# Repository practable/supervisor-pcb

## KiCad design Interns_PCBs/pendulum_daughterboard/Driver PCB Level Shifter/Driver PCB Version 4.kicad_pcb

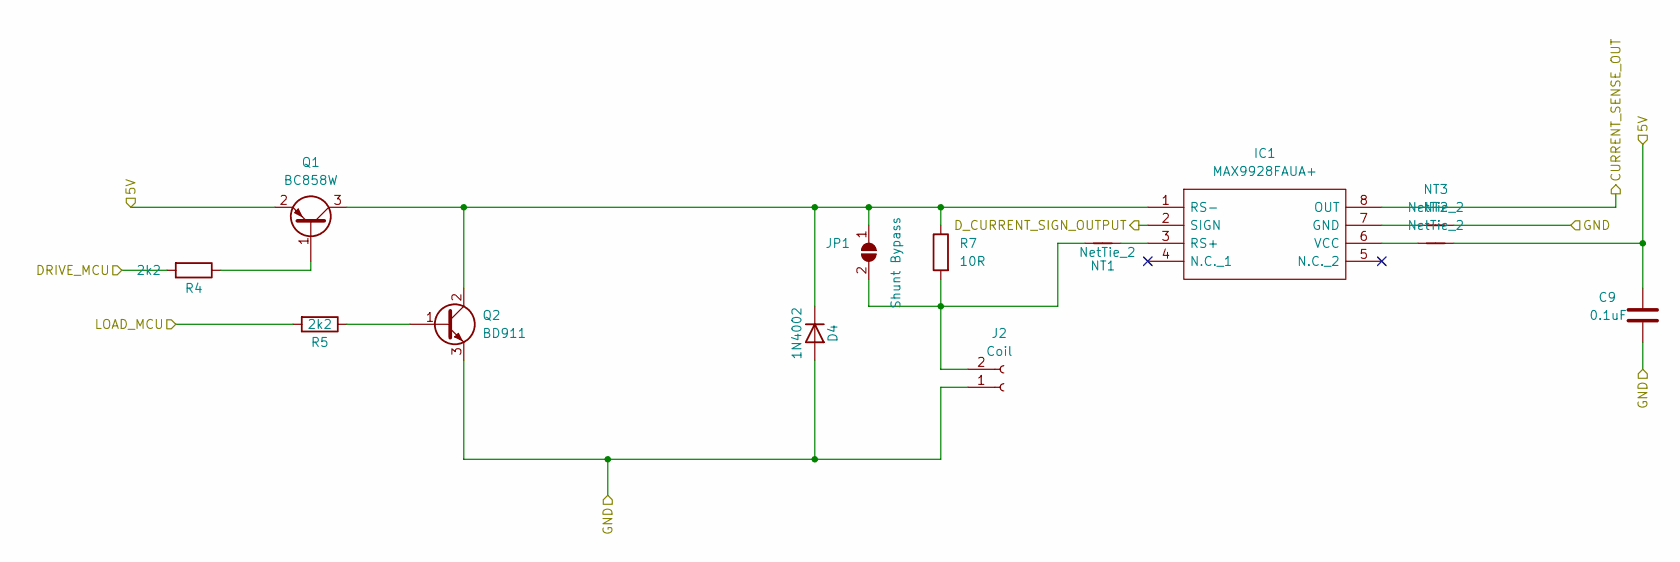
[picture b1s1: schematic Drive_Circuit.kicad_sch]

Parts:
C9: 0.1uF; C_0805_2012Metric_Pad1.18x1.45mm_HandSolder
D4: 1N4002; D_T-1_P5.08mm_Horizontal
IC1: MAX9928FAUA+; SOP65P490X110-8N; Manufacturer_Part_Number MAX9928FAUA+; Mouser Part Number 700-MAX9928FAUA
J2: Coil; RSPROPenduinoTerminal
JP1: Shunt Bypass; SolderJumper-2_P1.3mm_Open_Pad1.0x1.5mm
NT1, NT2, NT3: NetTie_2; NetTie-2_SMD_Pad0.5mm
Q1: BC858W; SOT-23
Q2: BD911; SOT-23
R4, R5: 2k2; R_0805_2012Metric_Pad1.20x1.40mm_HandSolder
R7: 10R; R_0805_2012Metric_Pad1.20x1.40mm_HandSolder

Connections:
DRIVE_GND: C9.2, D4.1 (A), J2.1, NT3.2, Q2.3 (E); also elsewhere on the board
DRIVE_OUT: R4.2; also elsewhere on the board
LOAD_OUT: R5.2; also elsewhere on the board
unnamed 13: D4.2 (K), IC1.1 (RS-), JP1.1 (A), Q1.3 (C), Q2.2 (C), R7.1; also elsewhere on the board
unnamed: IC1.7 (GND), NT3.1
unnamed 16: IC1.3 (RS+), NT1.2; also elsewhere on the board
unnamed 17: IC1.6 (VCC), NT2.1; also elsewhere on the board
unnamed: J2.2, JP1.2 (B), NT1.1, R7.2
unnamed: Q1.1 (B), R4.1
unnamed: Q2.1 (B), R5.1

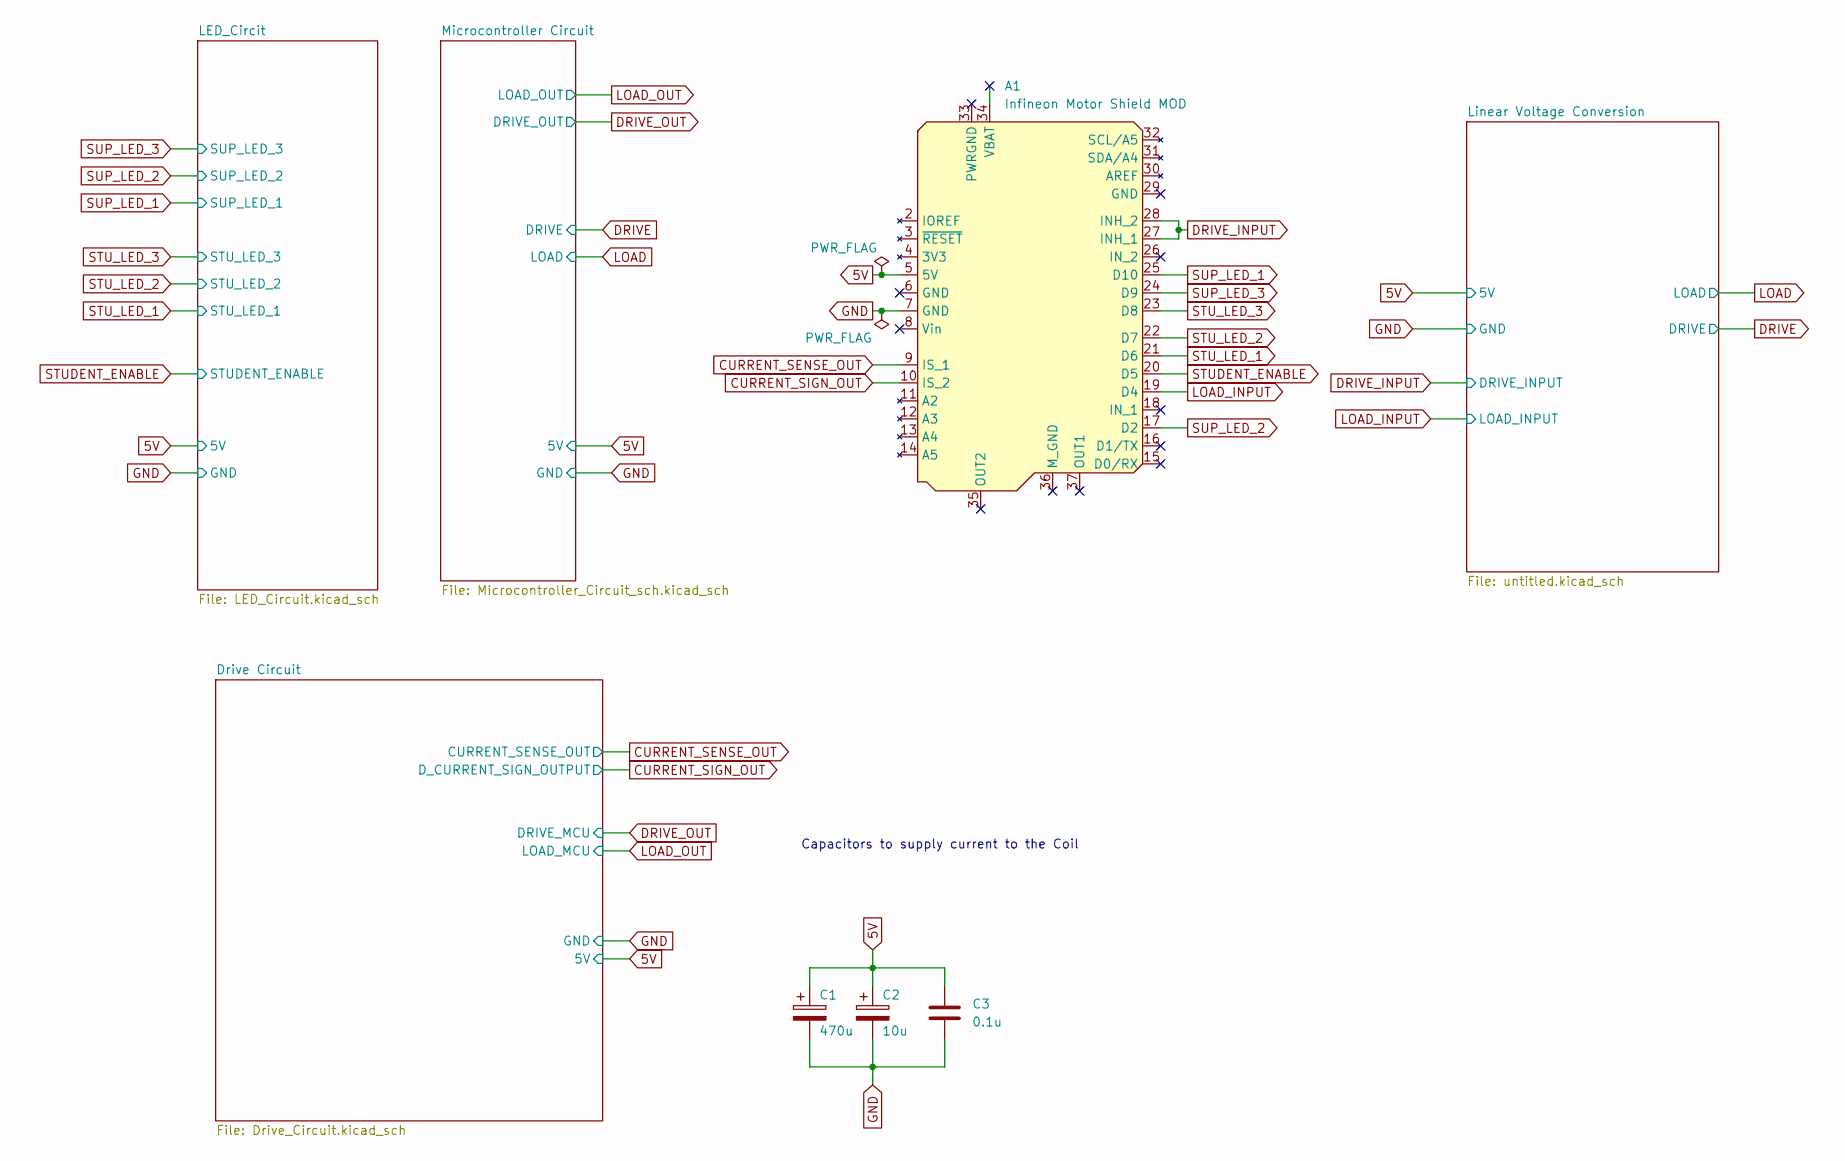
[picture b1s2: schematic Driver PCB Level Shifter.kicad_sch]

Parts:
A1: Infineon Motor Shield MOD; Infineon Motor Sheild hiddenPins
C1: 470u; C_Elec_8x10.2
C2: 10u; CP_Elec_3x5.3
C3: 0.1u; C_0805_2012Metric_Pad1.18x1.45mm_HandSolder

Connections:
CURRENT_SENSE_OUT: A1.9 (IS_1); also elsewhere on the board
CURRENT_SIGN_OUT: A1.10 (IS_2); also elsewhere on the board
DRIVE_GND: A1.7 (GND), C1.2, C2.2, C3.2; also elsewhere on the board
DRIVE_INPUT: A1.27 (INH_1), A1.28 (INH_2); also elsewhere on the board
LOAD_INPUT: A1.19 (D4); also elsewhere on the board
STUDENT_ENABLE: A1.20 (D5); also elsewhere on the board
STU_LED_1: A1.21 (D6); also elsewhere on the board
STU_LED_2: A1.22 (D7); also elsewhere on the board
STU_LED_3: A1.23 (D8); also elsewhere on the board
SUP_LED_1: A1.25 (D10); also elsewhere on the board
SUP_LED_2: A1.17 (D2); also elsewhere on the board
SUP_LED_3: A1.24 (D9); also elsewhere on the board

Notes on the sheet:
Capacitors to supply current to the Coil

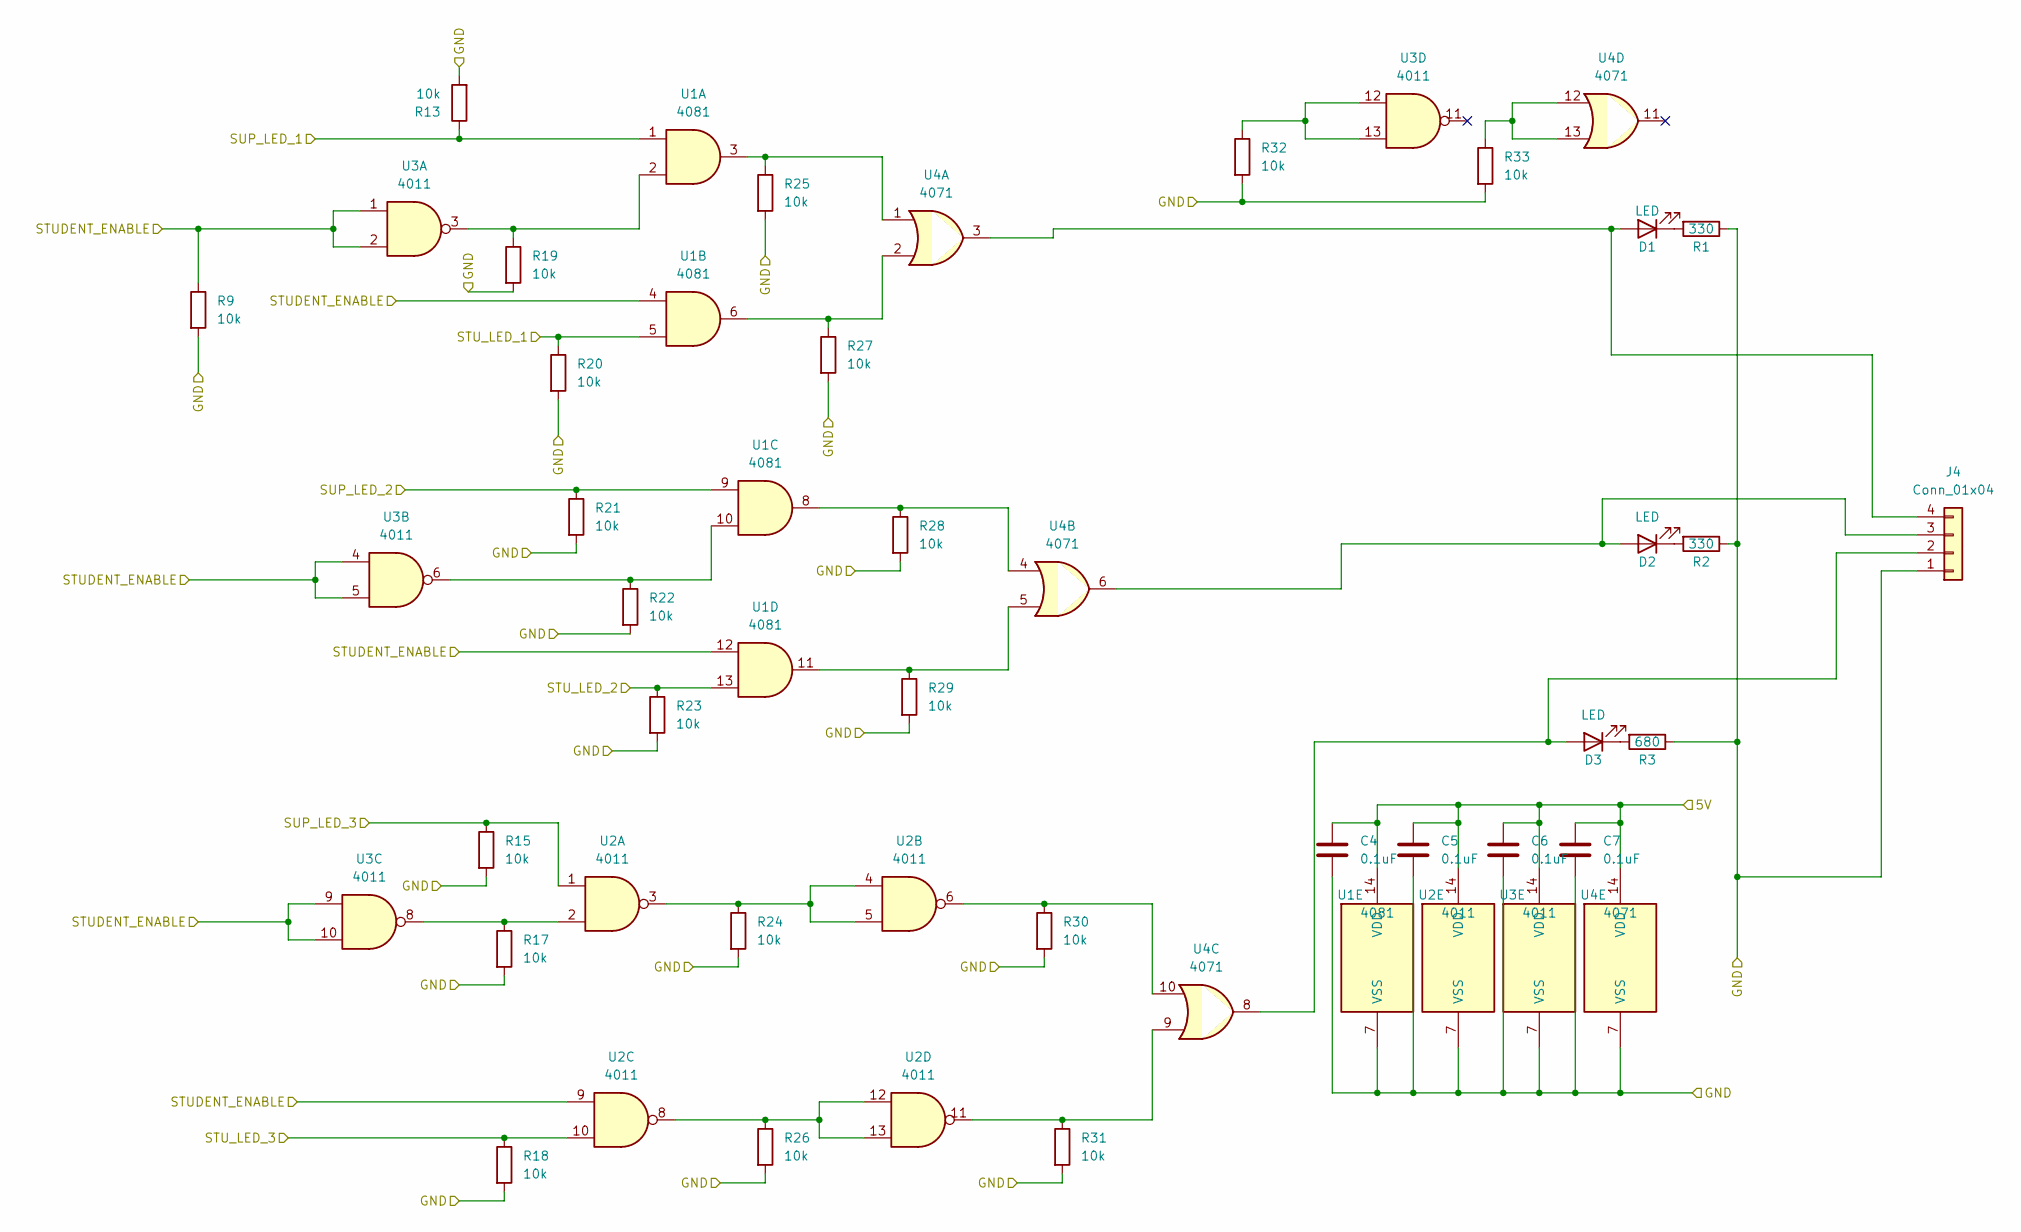
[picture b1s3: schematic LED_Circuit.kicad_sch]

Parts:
C4, C5, C6, C7: 0.1uF; C_0805_2012Metric_Pad1.18x1.45mm_HandSolder
D1, D2, D3: LED; LED_0805_2012Metric_Pad1.15x1.40mm_HandSolder
J4: Conn_01x04; PinHeader_1x04_P2.54mm_Vertical
R1, R2: 330; R_0805_2012Metric_Pad1.20x1.40mm_HandSolder
R3: 680; R_0805_2012Metric_Pad1.20x1.40mm_HandSolder
R9, R13, R15, R17, R18, R19, R20, R21, R22, R23, R24, R25, R26, R27, R28, R29, R30, R31, R32, R33: 10k; R_0805_2012Metric_Pad1.20x1.40mm_HandSolder
U1: 4081; SOIC127P600X175-14N
U2, U3: 4011; SOIC127P600X175-14N
U4: 4071; SOIC127P600X175-14N

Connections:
DRIVE_GND: C4.2, C5.2, C6.2, C7.2, J4.1, R1.1, R2.1, R3.1, R9.2, R13.2, R15.2, R17.2, R18.2, R19.2, R20.2, R21.2, R22.2, R23.2, R24.2, R25.2, R26.2, R27.2, R28.2, R29.2, R30.2, R31.2, R32.2, R33.2, U1.7 (VSS), U2.7 (VSS), U3.7 (VSS), U4.7 (VSS); also elsewhere on the board
unnamed: D1.1 (K), R1.2
unnamed: D1.2 (A), J4.4, U4.3
unnamed: D2.1 (K), R2.2
unnamed: D2.2 (A), J4.3, U4.6
unnamed: D3.1 (K), R3.2
unnamed: D3.2 (A), J4.2, U4.8
unnamed: R17.1, U2.2, U3.8
unnamed: R19.1, U1.2, U3.3
unnamed: R22.1, U1.10, U3.6
unnamed: R24.1, U2.3, U2.4, U2.5
unnamed: R25.1, U1.3, U4.1
unnamed: R26.1, U2.8, U2.12, U2.13
unnamed: R27.1, U1.6, U4.2
unnamed: R28.1, U1.8, U4.4
unnamed: R29.1, U1.11, U4.5
unnamed: R30.1, U2.6, U4.10
unnamed: R31.1, U2.11, U4.9
unnamed: R32.1, U3.12, U3.13
unnamed: R33.1, U4.12, U4.13
STUDENT_ENABLE: R9.1, U1.4, U1.12, U2.9, U3.1, U3.2, U3.4, U3.5, U3.9, U3.10; also elsewhere on the board
STU_LED_1: R20.1, U1.5; also elsewhere on the board
STU_LED_2: R23.1, U1.13; also elsewhere on the board
STU_LED_3: R18.1, U2.10; also elsewhere on the board
SUP_LED_1: R13.1, U1.1; also elsewhere on the board
SUP_LED_2: R21.1, U1.9; also elsewhere on the board
SUP_LED_3: R15.1, U2.1; also elsewhere on the board

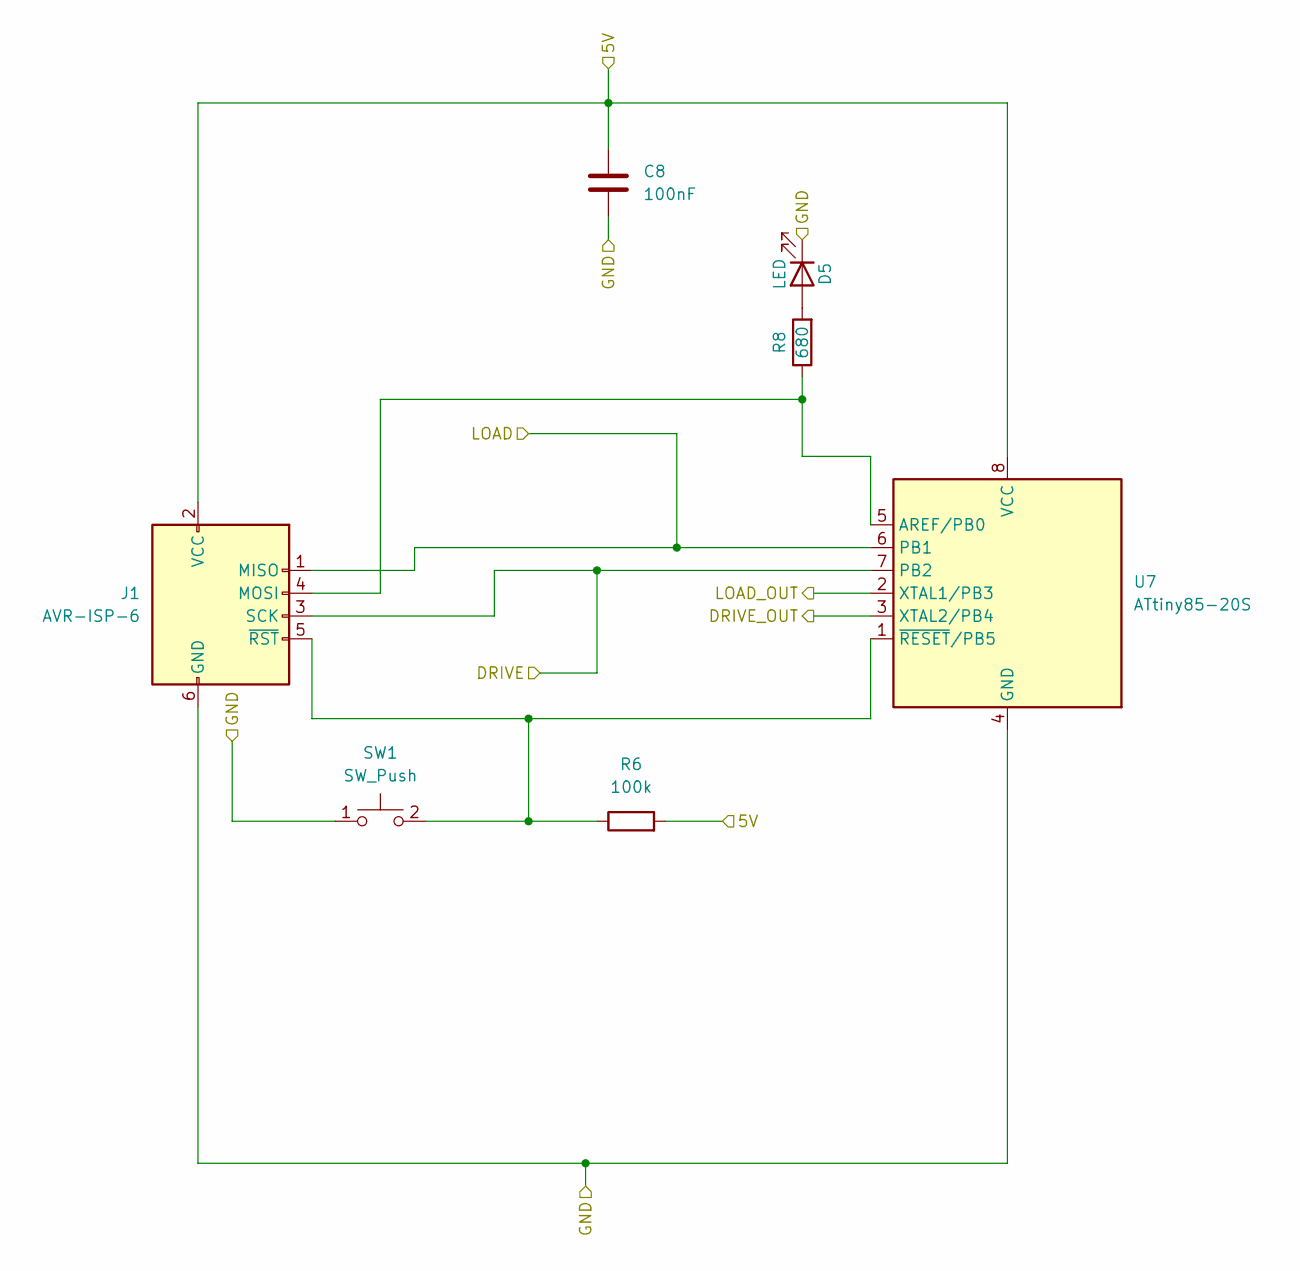
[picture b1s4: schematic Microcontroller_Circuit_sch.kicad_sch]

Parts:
C8: 100nF; C_0805_2012Metric_Pad1.18x1.45mm_HandSolder
D5: LED; LED_0805_2012Metric_Pad1.15x1.40mm_HandSolder
J1: AVR-ISP-6; PinHeader_2x03_P2.54mm_Vertical
R6: 100k; R_0805_2012Metric_Pad1.20x1.40mm_HandSolder
R8: 680; R_0805_2012Metric_Pad1.20x1.40mm_HandSolder
SW1: SW_Push; 13019319
U7: ATtiny85-20S; SOIC-8W_5.3x5.3mm_P1.27mm

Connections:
DRIVE_GND: C8.2, D5.1 (K), J1.6 (GND), SW1.1, U7.4 (GND); also elsewhere on the board
DRIVE_INPUT: J1.3 (SCK), U7.7 (PB2); also elsewhere on the board
LOAD_INPUT: J1.1 (MISO), U7.6 (PB1); also elsewhere on the board
unnamed: D5.2 (A), R8.2
unnamed 18: J1.4 (MOSI), R8.1, U7.5 (AREF/PB0); also elsewhere on the board
unnamed 19: J1.5 (~RST), R6.1, SW1.2, U7.1 (~RESET/PB5); also elsewhere on the board

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
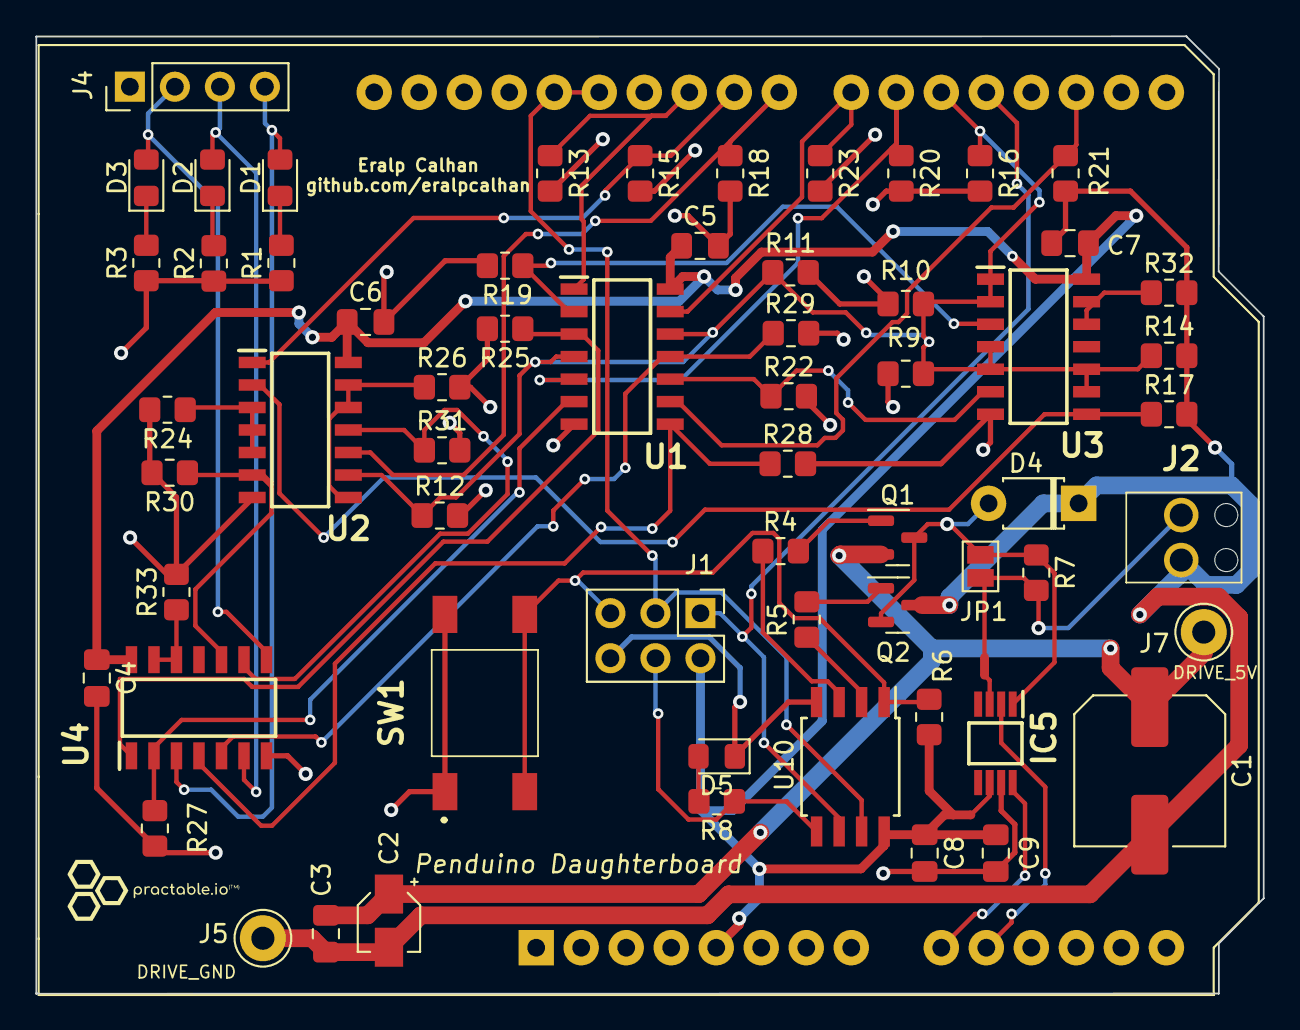
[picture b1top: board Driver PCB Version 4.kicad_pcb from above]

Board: 2 copper layers, 69.2 x 54.0 mm, 65 parts (0 on the bottom side), 44 nets.

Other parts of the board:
IC5: MAX9928FAUA+; SOP65P490X110-8N
J5: DRIVE_GND; Pin_D1.3mm_L11.0mm
J7: DRIVE_5V_IN; Pin_D1.3mm_L11.0mm
R10, R11, R12, R14, R16: 10k; R_0805_2012Metric_Pad1.20x1.40mm_HandSolder
U10: ATtiny85-20S; SOIC-8W_5.3x5.3mm_P1.27mm

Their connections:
CURRENT_SENSE_OUT: IC5.8 (OUT); also elsewhere on the board
CURRENT_SIGN_OUT: IC5.2 (SIGN); also elsewhere on the board
DRIVE_GND: IC5.7 (GND), J5.1, R10.2, R11.2, R12.2, R14.2, R16.2, U10.4 (GND); also elsewhere on the board
DRIVE_INPUT: U10.7 (PB2); also elsewhere on the board
DRIVE_OUT: U10.3 (XTAL2/PB4); also elsewhere on the board
LOAD_INPUT: U10.6 (PB1); also elsewhere on the board
LOAD_OUT: U10.2 (XTAL1/PB3); also elsewhere on the board
unnamed 13: IC5.1 (RS-); also elsewhere on the board
unnamed 16: IC5.3 (RS+); also elsewhere on the board
unnamed 17: IC5.6 (VCC); also elsewhere on the board
unnamed 18: U10.5 (AREF/PB0); also elsewhere on the board
unnamed 19: U10.1 (~RESET/PB5); also elsewhere on the board
STUDENT_ENABLE: R10.1, R11.1, R12.1, R14.1, R16.1; also elsewhere on the board

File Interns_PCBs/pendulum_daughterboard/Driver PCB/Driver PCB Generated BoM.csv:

"Source:","C:\Users\mcalhan\Documents\GitHub\RemoteLabs_Supervisor_PCB\pendulum_daughterboard\Driver PCB\Driver PCB.kicad_sch"
"Date:","23/06/2022 15:05:01"
"Tool:","Eeschema (6.0.5)"
"Generator:","C:\Program Files\KiCad\6.0\bin\scripting\plugins/bom_csv_grouped_by_value_with_fp.py"
"Component Count:","36"
"Ref","Qnty","Value","Cmp name","Footprint","Description","Vendor"
"A1, ","1","Infineon Motor Shield MOD","Infineon Motor Shield MOD","Audio_Module:Infineon Motor Sheild hiddenPins","Infineon Motor Driver Shield for Arduino Uno",""
"C1, ","1","460u","C_Polarized","Capacitor_SMD:C_0805_2012Metric_Pad1.18x1.45mm_HandSolder","Polarized capacitor",""
"C2, ","1","10u","C_Polarized","Capacitor_SMD:C_0805_2012Metric_Pad1.18x1.45mm_HandSolder","Polarized capacitor",""
"C3, ","1","0.1u","C","Capacitor_SMD:C_0805_2012Metric_Pad1.18x1.45mm_HandSolder","Unpolarized capacitor",""
"C4, C5, C6, C7, C8, ","5","100nF","C","Capacitor_SMD:C_0805_2012Metric_Pad1.18x1.45mm_HandSolder","Unpolarized capacitor",""
"C9, ","1","0.1uF","C","Capacitor_SMD:C_0805_2012Metric_Pad1.18x1.45mm_HandSolder","Unpolarized capacitor",""
"D1, D2, D3, ","3","LED","LED","LED_SMD:LED_0805_2012Metric_Pad1.15x1.40mm_HandSolder","Light emitting diode",""
"D4, ","1","1N4002","DIODE","Diode_SMD:D_0603_1608Metric_Pad1.05x0.95mm_HandSolder","Diode, anode on pin 1, for simulation only!",""
"IC1, ","1","AND GATES","CD74HC08QM96EP","ICPINS:SOIC127P600X175-14N","Enhanced Product Quadruple 2-Input Positive-And Gates",""
"IC2, ","1","NAND (Used as AND)","MC74ACT00DG","ICPINS:SOIC127P600X175-14N","ON SEMICONDUCTOR - MC74ACT00DG - IC, QUAD NAND GATE, 2I/P, SOIC-14",""
"IC3, ","1","NAND (Used as Inverter)","MC74ACT00DG","ICPINS:SOIC127P600X175-14N","ON SEMICONDUCTOR - MC74ACT00DG - IC, QUAD NAND GATE, 2I/P, SOIC-14",""
"IC4, ","1","OR ","MC74ACT00DG","ICPINS:SOIC127P600X175-14N","ON SEMICONDUCTOR - MC74ACT00DG - IC, QUAD NAND GATE, 2I/P, SOIC-14",""
"IC5, ","1","MAX9928FAUA+","MAX9928FAUA+","Sensor_Current:SOP65P490X110-8N","Maxim MAX9928FAUA+, Current Sensing Amplifier Single Bidirectional, Unidirectional 8-Pin uMAX",""
"J1, ","1","AVR-ISP-6","AVR-ISP-6","Connector_PinHeader_2.00mm:PinHeader_2x03_P2.00mm_Vertical","Atmel 6-pin ISP connector",""
"J2, ","1","Coil","Conn_01x02_Female","TerminalBlock_TE-Connectivity:TerminalBlock_TE_282834-2_1x02_P2.54mm_Horizontal","Generic connector, single row, 01x02, script generated (kicad-library-utils/schlib/autogen/connector/)",""
"J4, ","1","Conn_01x04","Conn_01x04","TerminalBlock_TE-Connectivity:TerminalBlock_TE_282834-4_1x04_P2.54mm_Horizontal","Generic connector, single row, 01x04, script generated (kicad-library-utils/schlib/autogen/connector/)",""
"J5, ","1","DRIVE_GND","Conn_01x01","Connector_Pin:Pin_D1.3mm_L11.0mm","Generic connector, single row, 01x01, script generated (kicad-library-utils/schlib/autogen/connector/)",""
"J7, ","1","DRIVE_5V_IN","Conn_01x01","Connector_Pin:Pin_D1.3mm_L11.0mm","Generic connector, single row, 01x01, script generated (kicad-library-utils/schlib/autogen/connector/)",""
"JP1, ","1","Shunt Bypass","SolderJumper_2_Open","Jumper:SolderJumper-2_P1.3mm_Open_Pad1.0x1.5mm","Solder Jumper, 2-pole, open",""
"Q1, ","1","BC557","BC557","Package_TO_SOT_SMD:SOT-523","0.1A Ic, 45V Vce, PNP Small Signal Transistor, TO-92",""
"Q2, ","1","BC547","BC547","Package_TO_SOT_SMD:SOT-523","0.1A Ic, 45V Vce, Small Signal NPN Transistor, TO-92",""
"R1, R2, R3, ","3","120","R","Resistor_SMD:R_0805_2012Metric_Pad1.20x1.40mm_HandSolder","Resistor",""
"R4, R5, ","2","2k2","R","Resistor_SMD:R_0805_2012Metric_Pad1.20x1.40mm_HandSolder","Resistor",""
"R6, ","1","100k","R","Resistor_SMD:R_0805_2012Metric_Pad1.20x1.40mm_HandSolder","Resistor",""
"R7, ","1","10R","R","Resistor_SMD:R_0805_2012Metric_Pad1.20x1.40mm_HandSolder","Resistor",""
"SW1, ","1","SW_Push","SW_Push","Button_Switch_SMD:13019319","Push button switch, generic, two pins",""
"U10, ","1","ATtiny85-20S","ATtiny85-20S","Package_SO:SOIC-8W_5.3x5.3mm_P1.27mm","20MHz, 8kB Flash, 512B SRAM, 512B EEPROM, debugWIRE, SOIC-8W",""

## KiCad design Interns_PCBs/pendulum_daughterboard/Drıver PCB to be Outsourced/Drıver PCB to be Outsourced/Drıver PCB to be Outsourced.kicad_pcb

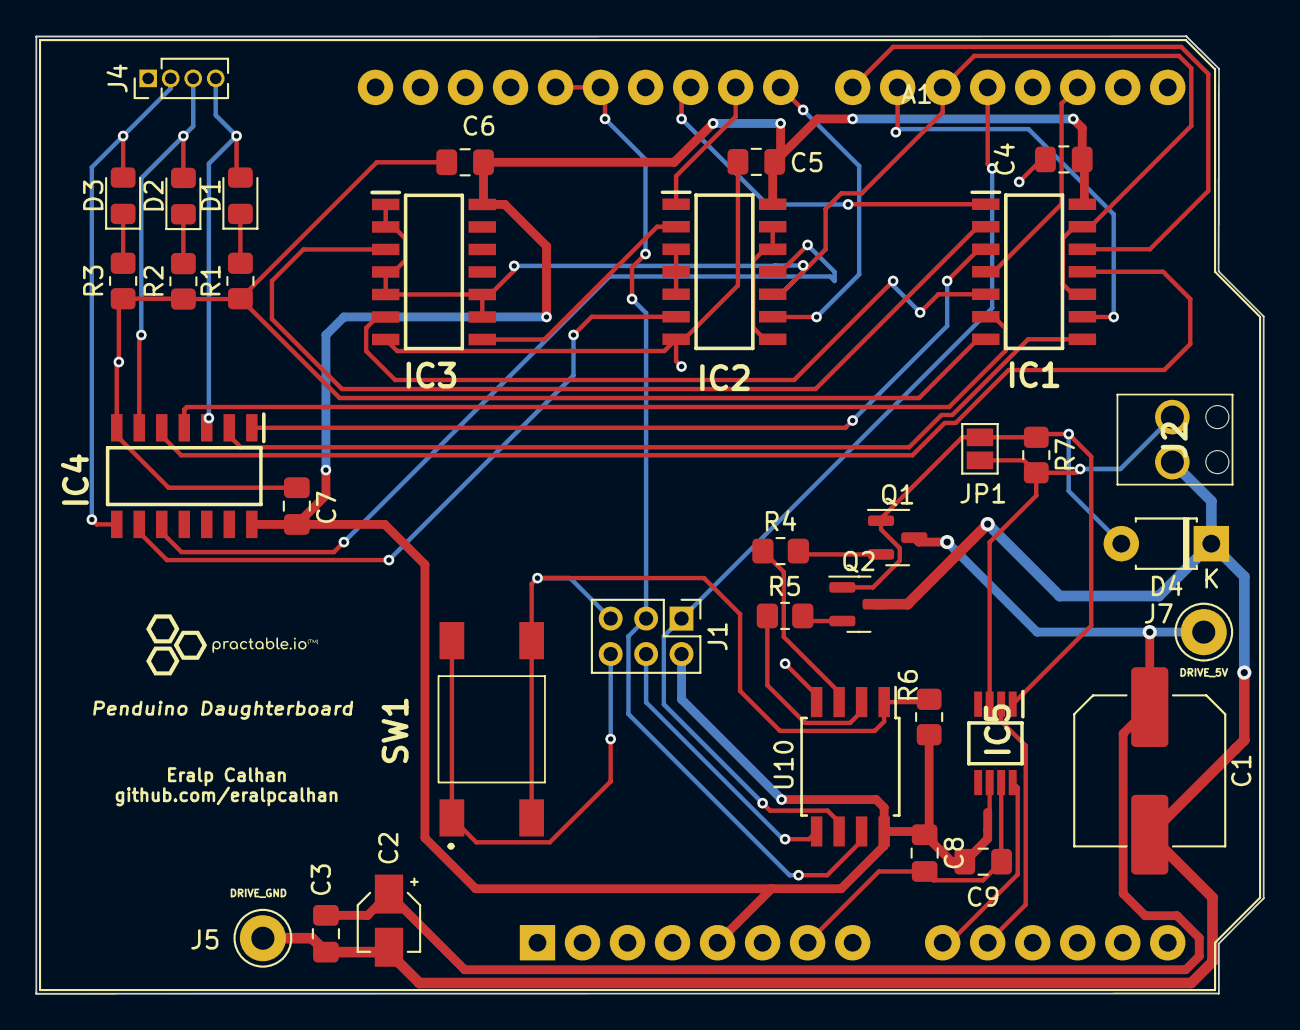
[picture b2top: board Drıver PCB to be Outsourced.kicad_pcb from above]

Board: 2 copper layers, 69.2 x 54.0 mm, 37 parts (0 on the bottom side), 41 nets.

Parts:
A1: Infineon Motor Shield MOD; Infineon Motor Sheild hiddenPins
C1: 470u; C_Elec_8x10.2
C2: 10u; CP_Elec_3x5.3
C3: 0.1u; C_0805_2012Metric_Pad1.18x1.45mm_HandSolder
C4, C5, C6, C7, C8: 100nF; C_0805_2012Metric_Pad1.18x1.45mm_HandSolder
C9: 0.1uF; C_0805_2012Metric_Pad1.18x1.45mm_HandSolder
D1, D2, D3: LED; LED_0805_2012Metric_Pad1.15x1.40mm_HandSolder
D4: 1N4002; D_T-1_P5.08mm_Horizontal
IC1: AND GATES; SOIC127P600X175-14N
IC2: NAND (Used as AND); SOIC127P600X175-14N
IC3: NAND (Used as Inverter); SOIC127P600X175-14N
IC4: OR; SOIC127P600X175-14N
IC5: MAX9928FAUA+; SOP65P490X110-8N
J1: AVR-ISP-6; PinHeader_2x03_P2.00mm_Vertical
J2: Coil; RSPROPenduinoTerminal
J4: Conn_01x04; PinHeader_1x04_P1.27mm_Vertical
J5: DRIVE_GND; Pin_D1.3mm_L11.0mm
J7: DRIVE_5V_IN; Pin_D1.3mm_L11.0mm
JP1: Shunt Bypass; SolderJumper-2_P1.3mm_Open_Pad1.0x1.5mm
NT1: NetTie_2; NetTie-2_SMD_Pad0.5mm
Q1: BC557; SOT-23
Q2: BC547; SOT-23
R1, R2, R3: 120; R_0805_2012Metric_Pad1.20x1.40mm_HandSolder
R4, R5: 2k2; R_0805_2012Metric_Pad1.20x1.40mm_HandSolder
R6: 100k; R_0805_2012Metric_Pad1.20x1.40mm_HandSolder
R7: 10R; R_0805_2012Metric_Pad1.20x1.40mm_HandSolder
SW1: SW_Push; 13019319
U10: ATtiny85-20S; SOIC-8W_5.3x5.3mm_P1.27mm

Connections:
AND_STU_LED_1: IC1.8 (3Y), IC4.2 (B1)
AND_STU_LED_2: IC1.11 (4Y), IC4.5 (B2)
AND_STU_LED_3: IC2.11 (Y4), IC4.10 (B3)
AND_SUP_LED_1: IC1.3 (1Y), IC4.1 (A1)
AND_SUP_LED_2: IC1.6 (2Y), IC4.4 (A2)
AND_SUP_LED_3: IC2.6 (Y2), IC4.9 (A3)
CURRENT_SENSE_OUT: A1.9 (IS_1), IC5.8 (OUT)
CURRENT_SIGN_OUT: A1.10 (IS_2), IC5.2 (SIGN)
DRIVE_5V: C1.1, C2.1, C3.1, J7.1, Q1.3 (E)
DRIVE_GND: C1.2, C2.2, C3.2, D4.1 (A), J2.1, J5.1, Q2.3 (E)
DRIVE_INPUT: A1.27 (INH_1), A1.28 (INH_2), J1.3 (SCK), U10.7 (PB2)
DRIVE_MCU: R4.2, U10.3 (XTAL2/PB4)
D_5V: A1.5 (5V), C4.1, C5.1, C6.1, C7.1, C8.1, C9.1, IC1.14 (VCC), IC2.14 (VCC), IC3.14 (VCC), IC4.14 (VCC), J1.2 (VCC), NT1.1, R6.2, U10.8 (VCC)
D_GND: A1.7 (GND), C4.2, C5.2, C6.2, C7.2, C8.2, C9.2, IC1.7 (GND), IC2.7 (GND), IC3.7 (GND), IC4.7 (GND), IC5.7 (GND), J1.6 (GND), J4.1, R1.1, R2.1, R3.1, SW1.1, U10.4 (GND)
INV_1: IC1.2 (1B), IC3.3 (Y1)
INV_2: IC1.5 (2B), IC3.6 (Y2)
INV_3: IC2.2 (B1), IC3.8 (Y3)
LOAD_INPUT: A1.19 (D4), J1.1 (MISO), U10.6 (PB1)
LOAD_MCU: R5.2, U10.2 (XTAL1/PB3)
unnamed: D1.1 (K), R1.2
unnamed: D2.1 (K), R2.2
unnamed: D3.1 (K), R3.2
unnamed: IC2.3 (Y1), IC2.4 (A2), IC2.5 (B2)
unnamed: IC2.8 (Y3), IC2.12 (A4), IC2.13 (B4)
unnamed: D4.2 (K), IC5.1 (RS-), JP1.1 (A), Q1.1 (C), Q2.1 (C), R7.1
unnamed: IC5.3 (RS+), J2.2, JP1.2 (B), R7.2
unnamed: IC5.6 (VCC), NT1.2
unnamed: J1.4 (MOSI), U10.5 (AREF/PB0)
unnamed: J1.5 (~RST), R6.1, SW1.2, U10.1 (~RESET/PB5)
unnamed: Q1.2 (B), R4.1
unnamed: Q2.2 (B), R5.1
OR_OUT_1: D1.2 (A), IC4.3 (Y1), J4.4
OR_OUT_2: D2.2 (A), IC4.6 (Y2), J4.3
OR_OUT_3: D3.2 (A), IC4.8 (Y3), J4.2
STUDENT_ENABLE: A1.20 (D5), IC1.10 (3B), IC1.13 (4B), IC2.10 (B3), IC3.1 (A1), IC3.2 (B1), IC3.4 (A2), IC3.5 (B2), IC3.9 (A3), IC3.10 (B3)
STU_LED_1: A1.21 (D6), IC1.9 (3A)
STU_LED_2: A1.22 (D7), IC1.12 (4A)
STU_LED_3: A1.23 (D8), IC2.9 (A3)
SUP_LED_1: A1.25 (D10), IC1.1 (1A)
SUP_LED_2: A1.17 (D2), IC1.4 (2A)
SUP_LED_3: A1.24 (D9), IC2.1 (A1)

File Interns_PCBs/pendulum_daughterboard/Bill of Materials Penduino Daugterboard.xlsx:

Component Name | Component ID | quantity | Value | Description | Vendor | Part Number | Link | Unit Price (ex. VAT) | Requisition Number | Ordered | Q Boards | Total Price
logic IC AND Gate | IC1 | 1 | NA |  | Farnell | MC74HC08ADG | https://uk.farnell.com/on-semiconductor/mc74hc08adg/ic-74hc-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 | 0.63 |  | No | 42 | 26.46
Logic IC OR Gate | IC2 | 1 | NA |  | Farnell | MC74HC32ADG | https://uk.farnell.com/on-semiconductor/mc74hc32adg/ic-74hc-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 | 0.56999999999999995 |  | No | 42 | 23.939999999999998
Logic IC NAND Gate | IC3 | 1 | NA |  | Farnell | MC74ACT00DG | https://uk.farnell.com/on-semiconductor/mc74act00dg/ic-quad-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 | 0.68 |  | No | 42 | 28.560000000000002
Logic IC NAND Gate | IC4 | 1 | NA |  | Farnell | MC74ACT00DG | https://uk.farnell.com/on-semiconductor/mc74act00dg/ic-quad-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 | 0.68 |  | No | 42 | 28.560000000000002
Current Sense Amplifier | IC5 | 1 | NA | Current Sense Amplifier | Farnell | MAX9928FAUA+ | https://uk.farnell.com/maxim-integrated-products/max9928faua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 | 1.88 |  | Yes | 42 | 78.959999999999994
LED Green | D1 | 1 | NA | Green LED | Farnell | MP008291 | https://uk.farnell.com/multicomp-pro/mp008291/led-green-70mc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 | 0.11 |  | No | 42 | 4.62
LED Orange | D2 | 1 | NA | Orange LED | Farnell | KPT-2012SECK | https://uk.farnell.com/kingbright/kpt-2012seck/led-orange-08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 | 0.12 |  | No | 42 | 5.04
LED Red | D3 | 1 | NA | Red LED | Farnell | MP008293 | https://uk.farnell.com/multicomp-pro/mp008293/led-red-220mcd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 | 0.1 |  | No | 42 | 4.2
Diode | D4 | 1 | NA |  | Farnell | 1N4002 | https://uk.farnell.com/multicomp/1n4002-t/diode-standard-rec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 | 0.13 |  | No | 42 | 5.46
Resistance | R1, R2, R3 | 3 | 120 | 120 OHM resistor for the LED circuit | Farnell | ERA6AEB121V | https://uk.farnell.com/panasonic/era6aeb121v/res-120r-0-125w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 | 0.27 |  | No | 42 | 34.020000000000003
Resistance | R4, R5 | 2 | 2k2 |  | Farnell | 1614917-1 | https://uk.farnell.com/neohm-te-connectivity/1614917-1/res-2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 | 0.17 |  | No | 42 | 14.280000000000001
Resistance | R6 | 1 | 100k |  | Farnell | RS73F2ATTD1003B | https://uk.farnell.com/koa-speer-electronics/rs73f2attd1003b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 | 0.18 |  | No | 42 | 7.56
Resistance | R7 | 1 | 10 |  | Farnell | 2-1614883-3 | https://uk.farnell.com/neohm-te-connectivity/2-1614883-3/res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 | 0.17 |  | No | 42 | 7.1400000000000006
Capacitor | C1 | 1 | 460u |  | Farnell | EEE1CA471UAP | https://uk.farnell.com/panasonic/eee1ca471uap/cap-470-f-16v-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 | 0.69 |  | No | 42 | 28.979999999999997
Capacitor | C2 | 1 | 10u |  | Farnell | AVE106M16A12T-F | https://uk.farnell.com/cornell-dubilier/ave106m16a12t-f/alum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 | 0.45 |  | No | 42 | 18.900000000000002
Capacitor | C3, C4, C5, C6,C7, C8, C9 | 7 | 100nF |  | Farnell | C0805C104K3RACTU | https://uk.farnell.com/kemet/c0805c104k3ractu/cap-0-1-f-25v-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 | 0.06 |  | No | 42 | 17.64
BJT PNP Transistor | Q1 | 1 | NA |  | Farnell | BC807-40LT1G | https://uk.farnell.com/on-semiconductor/bc807-40lt1g/trans-p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 | 0.18 |  | No | 42 | 7.56
BJT NPN Transistor | Q2 | 1 | NA |  | Farnell | BC817,215 | https://uk.farnell.com/nexperia/bc817-215/transistor-npn-45v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 | 0.25 |  | No | 42 | 10.5
AVR Programming Pin | J1 | 1 | NA |  | Farnell | 826925-3 | https://uk.farnell.com/amp-te-connectivity/826925-3/header-t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 | 0.69 |  | No | 42 | 28.979999999999997
2 way PCB terminal | J2 | 1 | NA |  | RS Components | 790-1098 | https://uk.rs-online.com/web/p/pcb-terminal-blocks/7901098 | 0.51200000000000001 |  | No | 42 | 21.504000000000001
4 way PCB terminal | J4 | 1 | NA |  | RS Components | 790-1102 | https://uk.rs-online.com/web/p/pcb-terminal-blocks/7901102 | 0.92400000000000004 |  | No | 42 | 38.808
Tactile Switch | SW1 | 1 | NA | Push Button | Farnell | 1301.9318.24 | https://uk.farnell.com/schurter/1301-9318-24/tactile-switch-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 | 0.42 |  | No | 42 | 17.64
ATtiny85-20S | U1 | 1 | NA | Microcontroller | RS Components | ATTINY85-20SF | https://uk.rs-online.com/web/p/microcontrollers/1717852/?rel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 | 1.8140000000000001 |  | No | 42 | 76.188000000000002
 |  |  |  |  |  |  |  |  |  |  |  | 535.5
